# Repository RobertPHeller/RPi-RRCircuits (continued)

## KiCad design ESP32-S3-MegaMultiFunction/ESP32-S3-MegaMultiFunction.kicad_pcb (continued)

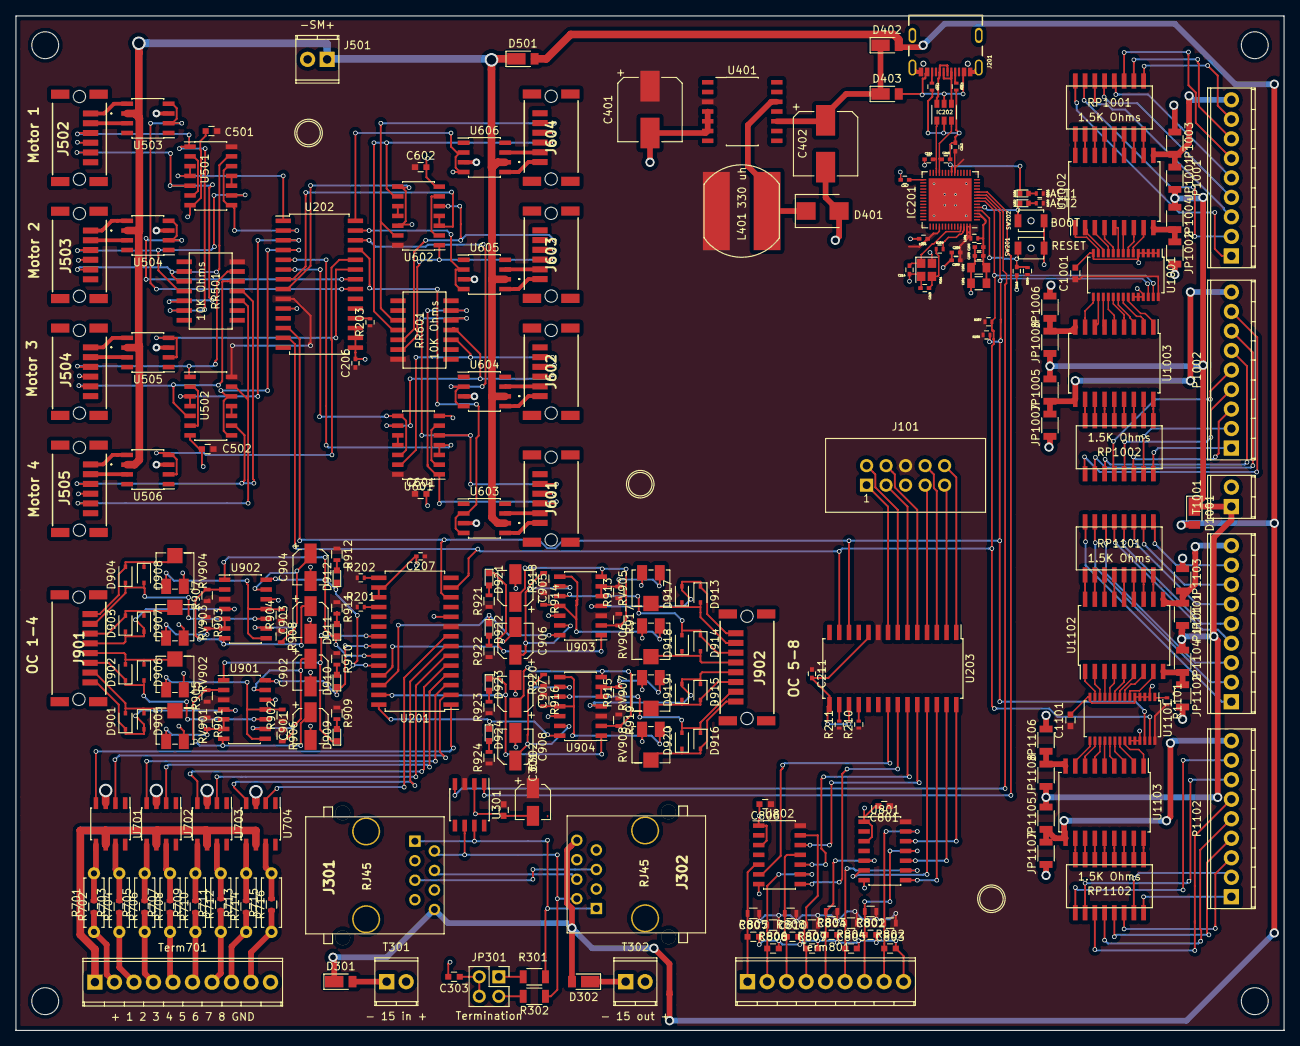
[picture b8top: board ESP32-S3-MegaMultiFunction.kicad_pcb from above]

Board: 2 copper layers, 165.1 x 132.1 mm, 245 parts (0 on the bottom side), 300 nets.

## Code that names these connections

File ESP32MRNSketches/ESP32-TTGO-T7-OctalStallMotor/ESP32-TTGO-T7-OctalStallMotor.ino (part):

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#define MotorPin GpioOutputSafeLow
#define SensePin GpioInputNP

GPIO_PIN(Motor1, MotorPin, 0);
GPIO_PIN(Motor2, MotorPin, 4);
GPIO_PIN(Motor3, MotorPin, 16);
GPIO_PIN(Motor4, MotorPin, 17);
GPIO_PIN(Motor5, MotorPin, 18);
GPIO_PIN(Motor6, MotorPin, 19);
GPIO_PIN(Motor7, MotorPin, 32);
GPIO_PIN(Motor8, MotorPin, 33);

GPIO_PIN(Points1, SensePin, 34);
GPIO_PIN(Points2, SensePin, 35);
GPIO_PIN(Points3, SensePin, 36);
GPIO_PIN(Points4, SensePin, 39);
GPIO_PIN(Points5, SensePin, 23);
GPIO_PIN(Points6, SensePin, 25);
GPIO_PIN(Points7, SensePin, 26);
GPIO_PIN(Points8, SensePin, 27);

// Create an initializer that can initialize all the GPIO pins in one shot
typedef GpioInitializer<Motor1_Pin, Motor2_Pin, Motor3_Pin, 
                        Motor4_Pin, Motor5_Pin, Motor6_Pin, 
                        Motor7_Pin, Motor8_Pin, Points1_Pin, 
                        Points2_Pin, Points3_Pin, Points4_Pin,
                        Points5_Pin, Points6_Pin, Points7_Pin,
                        Points8_Pin> GpioInit;

constexpr gpio_num_t CAN_RX_PIN = GPIO_NUM_4;
constexpr gpio_num_t CAN_TX_PIN = GPIO_NUM_5;

/// This is the primary entrypoint for the OpenMRN/LCC stack.
OpenMRN openmrn(NODE_ID);
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Logic l2(openmrn.stack()->node(),cfg.seg().logics().entry<1>(),openmrn.stack()->executor()->active_timers(),&l3);
Logic l1(openmrn.stack()->node(),cfg.seg().logics().entry<0>(),openmrn.stack()->executor()->active_timers(),&l2);

Turnout turnout1(openmrn.stack()->node(), cfg.seg().turnouts().entry<0>(),Motor1_Pin());
Turnout turnout2(openmrn.stack()->node(), cfg.seg().turnouts().entry<1>(),Motor2_Pin());
Turnout turnout3(openmrn.stack()->node(), cfg.seg().turnouts().entry<2>(),Motor3_Pin());
Turnout turnout4(openmrn.stack()->node(), cfg.seg().turnouts().entry<3>(),Motor4_Pin());
Turnout turnout5(openmrn.stack()->node(), cfg.seg().turnouts().entry<0>(),Motor5_Pin());
Turnout turnout6(openmrn.stack()->node(), cfg.seg().turnouts().entry<1>(),Motor6_Pin());
Turnout turnout7(openmrn.stack()->node(), cfg.seg().turnouts().entry<2>(),Motor7_Pin());
Turnout turnout8(openmrn.stack()->node(), cfg.seg().turnouts().entry<3>(),Motor8_Pin());

Points  points1(openmrn.stack()->node(), cfg.seg().points().entry<0>(),Points1_Pin());
Points  points2(openmrn.stack()->node(), cfg.seg().points().entry<1>(),Points2_Pin());
Points  points3(openmrn.stack()->node(), cfg.seg().points().entry<2>(),Points3_Pin());
Points  points4(openmrn.stack()->node(), cfg.seg().points().entry<3>(),Points4_Pin());
Points  points5(openmrn.stack()->node(), cfg.seg().points().entry<0>(),Points5_Pin());
Points  points6(openmrn.stack()->node(), cfg.seg().points().entry<1>(),Points6_Pin());
Points  points7(openmrn.stack()->node(), cfg.seg().points().entry<2>(),Points7_Pin());
Points  points8(openmrn.stack()->node(), cfg.seg().points().entry<3>(),Points8_Pin());


// The producers need to be polled repeatedly for changes and to execute the
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
    // Add the hardware CAN device as a bridge
    openmrn.add_can_port(
        new Esp32HardwareCan("esp32can", CAN_RX_PIN, CAN_TX_PIN));
}
                
void loop() {
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
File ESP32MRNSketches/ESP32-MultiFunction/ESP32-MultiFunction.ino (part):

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#define MotorPin GpioOutputSafeLow
#define SensePin GpioInputNP

GPIO_PIN(Motor1, MotorPin, 25);
GPIO_PIN(Motor2, MotorPin, 26);
GPIO_PIN(Motor3, MotorPin, 32);
GPIO_PIN(Motor4, MotorPin, 33);

GPIO_PIN(Points1, SensePin, 12);
GPIO_PIN(Points2, SensePin, 13);
GPIO_PIN(Points3, SensePin, 14);
GPIO_PIN(Points4, SensePin, 27);

#include "OccupancyDetector.h"

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
#define ButtonPin GpioInputNP

GPIO_PIN(Button1, ButtonPin, 0);
GPIO_PIN(Button2, ButtonPin, 2);
GPIO_PIN(Button3, ButtonPin, 15);
GPIO_PIN(Button4, ButtonPin, 16);

#include "LED.h"

#define LEDPin GpioOutputSafeLow

GPIO_PIN(LED1, LEDPin, 17);
GPIO_PIN(LED2, LEDPin, 18);
GPIO_PIN(LED3, LEDPin, 19);
GPIO_PIN(LED4, LEDPin, 23);

// Create an initializer that can initialize all the GPIO pins in one shot
typedef GpioInitializer<Motor1_Pin, Motor2_Pin, Motor3_Pin, 
Motor4_Pin, Points1_Pin, Points2_Pin, Points3_Pin, Points4_Pin,
OD1_Pin, OD2_Pin, OD3_Pin, OD4_Pin, Button1_Pin, Button2_Pin,
Button3_Pin, Button4_Pin, LED1_Pin, LED2_Pin, LED3_Pin, LED4_Pin> 
GpioInit;

constexpr gpio_num_t CAN_RX_PIN = GPIO_NUM_4;
constexpr gpio_num_t CAN_TX_PIN = GPIO_NUM_5;

/// This is the primary entrypoint for the OpenMRN/LCC stack.
OpenMRN openmrn(NODE_ID);
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Logic l2(openmrn.stack()->node(),cfg.seg().logics().entry<1>(),openmrn.stack()->executor()->active_timers(),&l3);
Logic l1(openmrn.stack()->node(),cfg.seg().logics().entry<0>(),openmrn.stack()->executor()->active_timers(),&l2);

Turnout turnout1(openmrn.stack()->node(), cfg.seg().turnouts().entry<0>(),Motor1_Pin());
Turnout turnout2(openmrn.stack()->node(), cfg.seg().turnouts().entry<1>(),Motor2_Pin());
Turnout turnout3(openmrn.stack()->node(), cfg.seg().turnouts().entry<2>(),Motor3_Pin());
Turnout turnout4(openmrn.stack()->node(), cfg.seg().turnouts().entry<3>(),Motor4_Pin());

Points  points1(openmrn.stack()->node(), cfg.seg().points().entry<0>(),Points1_Pin());
Points  points2(openmrn.stack()->node(), cfg.seg().points().entry<1>(),Points2_Pin());
Points  points3(openmrn.stack()->node(), cfg.seg().points().entry<2>(),Points3_Pin());
Points  points4(openmrn.stack()->node(), cfg.seg().points().entry<3>(),Points4_Pin());

OccupancyDetector oc1(openmrn.stack()->node(), cfg.seg().ocs().entry<0>(),OD1_Pin());
OccupancyDetector oc2(openmrn.stack()->node(), cfg.seg().ocs().entry<1>(),OD2_Pin());
OccupancyDetector oc3(openmrn.stack()->node(), cfg.seg().ocs().entry<2>(),OD3_Pin());
OccupancyDetector oc4(openmrn.stack()->node(), cfg.seg().ocs().entry<3>(),OD4_Pin());

Button button1(openmrn.stack()->node(), cfg.seg().buttons().entry<0>(),Button1_Pin());
Button button2(openmrn.stack()->node(), cfg.seg().buttons().entry<1>(),Button2_Pin());
Button button3(openmrn.stack()->node(), cfg.seg().buttons().entry<2>(),Button3_Pin());
Button button4(openmrn.stack()->node(), cfg.seg().buttons().entry<3>(),Button4_Pin());

LED led1(openmrn.stack()->node(), cfg.seg().leds().entry<0>(),LED1_Pin());
LED led2(openmrn.stack()->node(), cfg.seg().leds().entry<1>(),LED2_Pin());
LED led3(openmrn.stack()->node(), cfg.seg().leds().entry<2>(),LED3_Pin());
LED led4(openmrn.stack()->node(), cfg.seg().leds().entry<3>(),LED4_Pin());

// The producers need to be polled repeatedly for changes and to execute the
// debouncing algorithm. This class instantiates a refreshloop and adds the two
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    
    // Add the hardware CAN device as a bridge
    openmrn.add_can_port(
           new Esp32HardwareCan("esp32can", CAN_RX_PIN, CAN_TX_PIN));
    Serial.println("Added the hardware CAN device as a bridge...");
}
                
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
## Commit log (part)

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2021-10-12 Update quad MCP23017 node
2021-10-12 Make BlinkTimer a Singleton
2021-10-12 Updates to ESP32-PWMHalfSiding code [adding in debug code and updates to Blink handling.
2021-10-12 Final bug fixes for ESP32-PWMHalfSiding.ino
2021-10-20 Trying to isolate the 4 driver outputs.
2021-10-20 Isolate the AUX LED/device buffer power.
2021-10-22 Isolate buffer outputs from +12 supply. on the Pocket Beagle Multifunction Board.
2021-10-24 Fixes to MegaIOOpenMRN 64 Line Hardware.hxx.
2021-10-27 Bug fixes for MegaIOOpenMRN.
2021-11-08 Fix instance for GPIO pins.
2021-11-29 Nearly working node code
2021-11-30 Updates to ESP32-PWMHalfSidingSMD: I2C pullups, alt. SCL pins.
2021-12-03 Added CallableFlow to initialize variable values.
2021-12-05 Change MegaIOOpenMRN to use GC over Tcp/Ip
2021-12-06 Completed debugging ESP32-PWMHalfSiding.ino.
2021-12-17 Updated ESP32-PWMHalfSidingSMD
2021-12-27 PCBWayBOM.
2021-12-27 Updating ESP32-PWMHalfSidingSMD documentation.
2022-01-11 Add I2C pullups to ESP32-MultiFunction.
2022-01-11 Remove section for Crossing with Interchange.
2022-01-14 Add r0oland/ESP32_mini_KiCad_Library
2022-01-18 Add TTGO-T7 version of ESP32-PWMHalfSidingSMD.
2022-01-21 Kit booklet cover.
2022-02-26 Added ESP32 Octal Stall Motor
2022-02-26 Add firmware for ESP32-TTGO-T7-OctalStallMotor
2022-02-27 Added VetoBitEventInterface.
2022-03-01 Add Veto, Logic, and TrackCircuits.
2022-03-05 Complete ESP32-TTGO-T7-OctalStallMotor PCB, start breadboard.
2022-03-05 Add ESP32-TTGO-T7-OctalCTSense PCB.
2022-03-05 Add code for ESP32-TTGO-T7-OctalCTSense
2022-03-07 Breadboard for ESP32-TTGO-T7-OctalCTSense
2022-05-21 Update libraries
2022-05-21 Updated to PocketBeagleCommandStation_SMD
2022-05-21 Tiva MultiFunction board completed.
2022-05-31 Reroute an I/O, add documentation.
2022-06-17 Add ESP32-D0WDQ6 Component and footprint libraries.
2022-06-17 Add ESP32-D0WD-V3 component and footprint.
2022-06-18 Initial draft of bare-chip ESP32 Multifunction board.
2022-06-19 All but the MPU on the ESP32-D0WD-V3-MultiFunction is done.
2022-06-20 Completed ESP32-D0WD-V3-MultiFunction.
2022-06-20 Start on ESP32-D0WD-V3-USBProgBoard.
2022-06-21 Created ESP32-D0WD-V3-USBProgBoard.
2022-06-22 Add prog header silk screen markings.
2022-06-23 Start ESP32-D0WD-V3-MultiFunctionOpenMRNIDF.
2022-06-23 Main esp32multifunction C++ code started.
2022-06-23 Add I/O helper code (copied from elsewhere).
2022-06-23 Fix incorrect I/O pin assignments.
2022-06-24 Add PCA9685 driver.
2022-06-25 Remove unneeded file: CDIClient.hxx.
2022-06-25 Fixed all compilation errors (I think).
2022-06-26 Code compiles to completion.
2022-07-16 Cosmetic updates: copyright, labels, etc.
2022-07-16 Generate Gerbers.
2022-07-17 Updates -- additional non-SMD, Mouser company codes.
2022-07-17 Final touches on USB prog board.
2022-07-18 Add BootPauseHelper.
2022-07-19 Finish up BootPauseHelper.
2022-07-20 Refactor for passing the nodeid on the command line.
2022-07-22 Cosmetic updates to PocketBeagleCommandStation_SMD.
2022-07-25 Update to possible include through hole assembly at PCBWAY.
2022-07-29 Fixed footprints for DFLS240-7s.
2022-07-30 Updated BOM files.
2022-08-23 Completed ESP32-S3-MultiFunction firmware.
2022-08-23 Restore Act2 LED (double up on GPIO0 [boot pin]).
2022-08-23 Cleaned up silk.
2022-08-23 Updated processor part number.
2022-08-23 Clean up silk.
2022-08-24 Adjust 3D shapes and create 3D image.
2022-08-24 Add ESD and Bypass caps (PocketBeagle Command Station).
2022-08-24 Clean up silk, minor adjustments, and add missing 3d shapes to PB Command Station.
2022-08-24 Finalize part numbers.
2022-08-25 Add symbols and copywrite notice.
2022-08-25 Create schematic PDF.
2022-08-25 Minor typo fix.
2022-08-26 Add ThruHolePos.
2022-08-26 Minor update.
2022-08-26 Remove a debug statement.
2022-08-27 Start on a Booster Node.
2022-08-27 Fix minor part number and footprint error.
2022-08-27 Initial start for ESP32-C3-Booster.
2022-08-28 Replace D_Shockley with D_Schottky.
2022-08-28 Completed first pass ESP32-C3-Booster.
2022-08-29 Finalize ESP32-C3-Booster: mounting holes, Fids, copyright and symbols/logos, silk cleanup.
2022-08-29 Starting on the documentation.
2022-08-30 Add Power Labels.
2022-08-30 Add DCC Signal Labels.
2022-08-30 Updates to the Alt_H and Alt_L input handling in the Booster.
2022-08-30 Working on the kitbooklet for ESP32-S3-MultiFunction.
2022-08-31 Update configuration as per Mike Dunston's suggestions.
2022-08-31 Completed through Logic configuration.
2022-08-31 Added Veto version of the Turnout GPIO.
2022-08-31 Adjust power labeling and change the LCC logo to a larger version.
2022-08-31 Fleshing out the documentation.
2022-09-01 Add a terminal block to provide external stall motor power.
2022-09-01 Update 3D package (power supply).
2022-09-01 Minor (cosmetic) fixes.
2022-09-01 Starting on the App Notes.
2022-09-01 Embed all fonts.
2022-09-02 Add Yard Ladder to app notes.
2022-09-02 Rename YardLadder.png to ESP32S3-YardLadder.png
2022-09-02 Add wiring to to ABSTrack_Stacked.
2022-09-04 Working on ESP32-S3-MultiFunction documentation.
2022-09-04 Add ESP32-PWMHalfSidingOpenMRNIDF.
2022-09-04 Debugging esp32pwmhalfsiding.
2022-09-05 Bump up stack size to allow to dynamic CDI needs.
2022-09-05 Increase stack and add in polling setup.
2022-09-05 Remove duplicate OpenMRNIDF component dirs and create a common OpenMRNIDF component dir.
2022-09-06 Change BitEventPC to BitEventProducer in PolledProducerNoDebouncer.
2022-09-06 Working on documentation...
2022-09-08 Part counter.
2022-09-09 Minor updates.
2022-09-09 Started on LPC1754-MultiIOBoard.
2022-09-10 Working on LPC1754-MultiIOBoard.
2022-09-10 Add additional footprints.
2022-09-11 Assorted cosmetic fixes (symbols, logo, copyright, etc.)
2022-09-11 Add Power LED and Reset button.
2022-09-11 Start on the firmware for LPC1754-MultiIOBoard.
2022-09-12 Working on build infrastructure for LPC1758-MultiIOBoardOpenMRN.
2022-09-12 Working on LPC1758 Multi I/O Board firmware.
2022-09-12 Completed *bare* firmware.
2022-09-13 Add activity LEDs.
2022-09-13 Working on the firmware for LPC1758-MultiIOBoard.
2022-09-14 Add NVS support.
2022-09-14 Completed LPC1758 Multi I/O Board
2022-09-15 LPC1768 Multi IO Board circuit design completed.
2022-09-16 Start on the PCB.
2022-09-16 Completed PCB for LPC1768 Multi IO Board.
2022-09-17 Clean up silk screen.
2022-09-17 Adjustments to breadboard target.
2022-09-21 Completed basic run tests of esp32multifunction.
2022-09-21 Add missing files, add logging to main.cxx.
2022-09-22 Complete Common MCU LCC board.
2022-09-22 Starting on LPC176x_MultiFunction.
2022-09-23 Working on LPC176x_MultiFunction.
2022-09-23 Almost done with the schematic.
2022-09-25 Completed LPC176x_MultiFunction: TODO: cleanup Silk and Fab, add copyright, labels, etc.
2022-09-25 Completed LPC176x MultiFunction board.
2022-09-25 Start on ESP32-C3-Booster firmware.
2022-09-25 Start on LPC176x_MultiFunction firmware.
2022-09-26 Started on Esp32C3Booster.
2022-09-26 Handle missing declaration...
2022-09-26 Updated OpenMRNIDF.
2022-09-26 Updated ADCWrapper.hxx for updated OpenMRNIDF.
2022-09-26 Started LPC176x_MultiFunctionOpenMRN.
2022-09-27 Completed first draft of LPC176x MultiFunction board.
2022-09-27 Minor Makefile changes, remove items that should not be under version control.
2022-09-28 Check for configuration corruption.
2022-09-28 Update hardware pin assignments.
2022-09-29 Add UniversalLCCNodeBreakout.
2022-09-29 Final tweaks.
2022-09-29 Update master README.md.
2022-10-02 Cannot declare factory_reset_helper staticly if SimpleCanStack is not devlared staticly.
2022-10-02 Debugginh LPC176x_MultiFunctionOpenMRN.
2022-10-04 Refactoring IO Class Instances.
2022-10-04 Refactor IO classes.
2022-10-04 Working on I2C driver for the LPC17xx_40xx.
2022-10-04 Refactor Mast to shrink memory usage.
2022-10-05 Working on slimming memory.
2022-10-06 Debugged LPC17xx_40xxI2C.cxx.
2022-10-06 Working on EEProm / factory_reset() issues.
2022-10-07 Further debugging of LPC176x_MultiFunctionOpenMRN.
2022-10-07 Start on ESP32-S3/LCC SMINI replacement.
2022-10-08 Completed ESP32-S3-MultiIO (LCC SMINI replacement).
2022-10-08 Completed (untested) firmware for ESP32-S3-MultiIO.
2022-10-09 Remove unneeded pullups.
2022-10-09 Added ESP32-S3 Mega MultiFunction.
2022-10-10 First four motors done.
2022-10-10 Completed Stall Motors.
2022-10-11 Completed ODs and LED/Drivers.
2022-10-11 Moved LCC/CAN transceiver circuit.
2022-10-11 ESP32-S3-MegaMultiFunction is basically complete. TODO: clean up silk and fab.
2022-10-12 Move dims to User Dwg layer.
2022-10-12 First good build of esp32megamultifunction.
2022-10-13 Add USB-A (host) connector.
2022-10-13 Working up a BOM for PocketBeagleCommandStation.
2022-10-14 Complete BOM, Add fuses.
2022-10-14 Create fab files for the heat sink (PocketBeagleCommandStation).
2022-10-19 Finalize BOM, clean up silk.
2022-10-19 Make all TP's visible on the silk.
2022-10-24 Place FD.
2022-10-27 Update 3D shapes for PocketBeagleCommandStation PDB.
2022-10-29 BOM adjustments for the SMD version of the PocketBeagle Command Station.
2022-11-03 Add Schematic PDFs and board renderings for PocketBeagle Command Station desgines.
2022-11-04 Add WiThrottle support to BBBCommandStationOpenMRN.
2022-11-05 Add fan part number.
2022-11-05 Update 3D shapes on ESP32-C3-Booster.
2022-11-05 Add README, Schematic, Board Rendering, and BOM for ESP32-C3-Booster.
2022-11-06 Update 3D shapes for LCC CAN CAPE.
2022-11-06 Add H0 Yard Ladder
2022-11-06 Add Prog track to N yard ladder.
2022-11-13 Update README.md files.
2022-11-14 Updates to README.md files.
2022-11-15 Updating documentation (Yard Ladder).
2022-11-16 Embed fonts in the schematic.
2022-11-16 Split schematic into separate pages.
2022-11-16 Add Heatsink files.
2022-11-16 Update README.
2022-11-16 Add documentation files to BBBCommandStationOpenMRN.
2022-11-16 Add missing resistors on the bases of Q3 and Q4.
2022-11-17 Updating documentation.
2022-11-17 Updating documentation (fix copyrights).
2022-11-27 Move to proper I2C driver.
2022-12-01 Add ESP32-S3-WROOM footprint.
2022-12-03 WROOM module Version.
2022-12-08 Add WROOM modules. Change the ESP32-C3 booster to us the ESP32-C3-WROOM module.
2022-12-12 Update to new PBs.
2022-12-15 ESP32 S3 MultiFunction OpenMRNIDF updates.
2022-12-15 Static CDI XML support.
2022-12-20 Remove VFS from I2C driver.
2022-12-20 sdkconfig updates.
2022-12-20 Add dummy files to make git include empty dirs.
2022-12-23 Working on PWM driver...
2022-12-24 Refactor ESP32-PWMHalfSidingOpenMRNIDF.
2022-12-24 Minor updates to ESP32-S3-MultiFunctionOpenMRNID.
2022-12-25 Add test signal lamp boot flag, fix PCA9685PWM bug (incorrecort constructor for lamp control struct).
2022-12-26 Update PCA9685PWM and add SignalLampTester.
2022-12-31 Remove Command Stations and Boosters (move to new repo).
2022-12-31 Cleanup ESP32 files.
2022-12-31 Cleanup ESP32.
2023-10-27 Add Missing upgrade files.
2023-11-22 Add 3D shapes to SMD version.
2023-11-22 Create Kit booklet for LCCCANCape_SMD.
2024-01-04 Add 3D model.
2024-04-25 Update for tcllib1.21 and new part numbers.
2024-04-25 Part number updates.
2024-04-26 Updates to KiCadBOM2PCBWayBOM.
2024-04-29 Minor PCB adjustments. Firmware fixes.
2024-04-30 Final tweaks to the firmare.
2024-04-30 Misc. fixes.
2024-04-30 Add spiffs library for stm32f767xx.
2024-04-30 Add missing 3D shapes. Update documentation.
2024-04-30 Add ST_Morpho to throughHole parts.
2024-04-30 Add dims.
2024-05-01 Complete kitbooklet.
2024-05-01 Add plus signs to power terminal marking (show polarity).
2024-05-01 Add in node ID configuration and documentation updates.
2024-05-02 Documentation updates.
2024-05-02 Minor build infraestructure updates.
2024-05-03 Minor updates to the PCB.
2024-05-03 Finishing touches to the documentation.
2024-05-03 Adjust track pickup pads.
2024-05-03 Work on Kit Booklet.
2024-05-04 Continuing with kit booklet.
2024-05-04 Completed drift of the kit booklet.
2024-06-03 Complete STM32F767ZI_LCC_Repater board.
2024-06-03 Add flash and debug targets.
2024-06-03 Rename STM32F767ZI_LCC_Repeater.
2024-06-07 Complete documentation.
2024-09-02 Tweaks to FRED.
2024-09-05 Updates to BOM processing.
2025-08-24 Add Simple BeagleBone Black I/O Cape.
